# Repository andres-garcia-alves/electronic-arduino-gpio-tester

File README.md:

# Arduino GPIO Tester

Electronic proyect for easy test of Arduino Nano/UNO analog and digital (GPIO) pins.  

&nbsp;

This project use the following electronic components:
- 1 x Arduino Nano v3.0
- 2 x Connector pins
- 22 x LED 3mm
- 22 x 1k ohm resistors

&nbsp;

### Screenshots

| Diagram - Schematics                            | Diagram - PCB                                   |
|-------------------------------------------------|-------------------------------------------------|
|          |                |

| Diagram - PCB Render                            | Diagram - PCB Render                            |
|-------------------------------------------------|-------------------------------------------------|
|      |       |

| Prototype                                       | PCB Manufacturing                               |
|-------------------------------------------------|-------------------------------------------------|
|          |          |

| PCB Assembly                                    | Project Assembly                                |
|-------------------------------------------------|-------------------------------------------------|
|          |          |

| Project Final                                   | Project Final (YouTube video)                   |
|-------------------------------------------------|-------------------------------------------------|
|          |          |

See 'Rescources' sub-folder for more pictures & videos of the project.

&nbsp;

### Version History

v1.0 (2023.05.13) - Initial release.  
v1.1 (2023.05.16) - Bug fixes.  

&nbsp;

This source code is licensed under GPL v3.0  
Please send me your feedback about this project: andres.garcia.alves@gmail.com

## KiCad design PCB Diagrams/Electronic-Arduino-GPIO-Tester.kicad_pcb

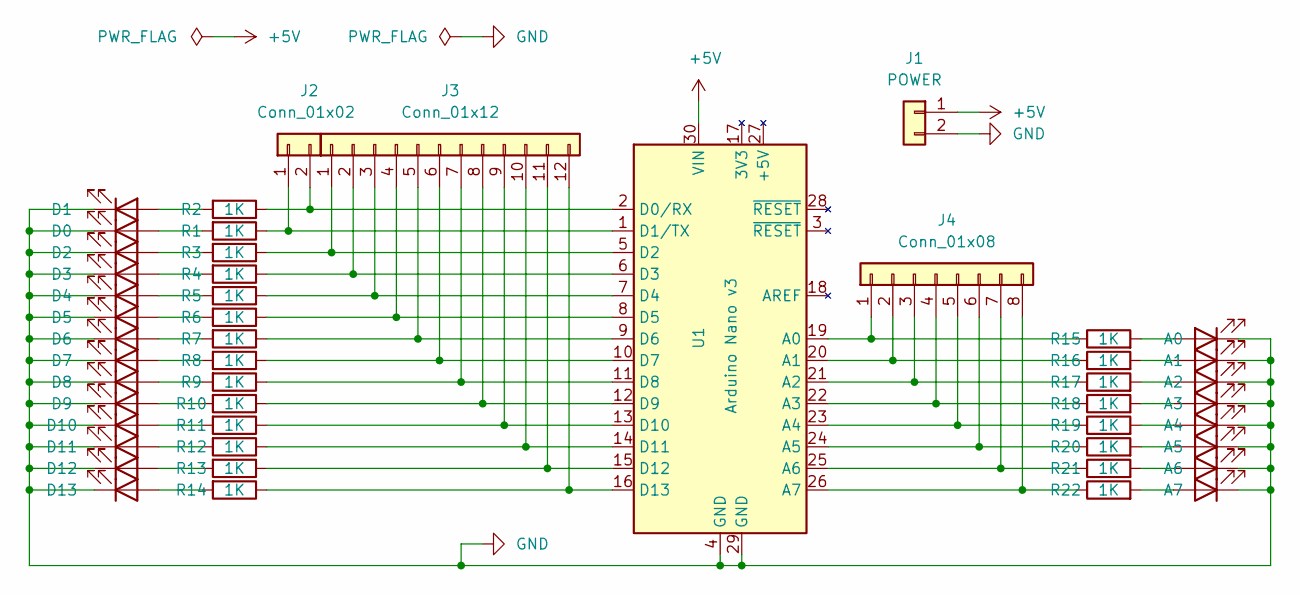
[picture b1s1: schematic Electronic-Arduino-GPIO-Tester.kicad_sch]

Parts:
A0, A1, A2, A3, A4, A5, A6, A7: LED; LED_D3.0mm
D0, D1, D2, D3, D4, D5, D6, D7, D8, D9, D10, D11, D12, D13: LED; LED_D3.0mm
J1: POWER; PinHeader_1x02_P2.54mm_Horizontal
J2: Conn_01x02; PinSocket_1x02_P2.54mm_Vertical
J3: Conn_01x12; PinSocket_1x12_P2.54mm_Vertical
J4: Conn_01x08; PinSocket_1x08_P2.54mm_Vertical
R1, R2, R3, R4, R5, R6, R7, R8, R9, R10, R11, R12, R13, R14, R15, R16, R17, R18, R19, R20, R21, R22: 1K; R_Axial_DIN0207_L6.3mm_D2.5mm_P7.62mm_Horizontal
U1: Arduino Nano v3; Arduino_Nano

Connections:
+5V: J1.1, U1.30 (VIN)
GND: A0.1 (K), A1.1 (K), A2.1 (K), A3.1 (K), A4.1 (K), A5.1 (K), A6.1 (K), A7.1 (K), D0.1 (K), D1.1 (K), D2.1 (K), D3.1 (K), D4.1 (K), D5.1 (K), D6.1 (K), D7.1 (K), D8.1 (K), D9.1 (K), D10.1 (K), D11.1 (K), D12.1 (K), D13.1 (K), J1.2, U1.4 (GND), U1.29 (GND)
unnamed: A0.2 (A), R15.2
unnamed: A1.2 (A), R16.2
unnamed: A2.2 (A), R17.2
unnamed: A3.2 (A), R18.2
unnamed: A4.2 (A), R19.2
unnamed: A5.2 (A), R20.2
unnamed: A6.2 (A), R21.2
unnamed: A7.2 (A), R22.2
unnamed: D0.2 (A), R1.2
unnamed: D1.2 (A), R2.2
unnamed: D2.2 (A), R3.2
unnamed: D3.2 (A), R4.2
unnamed: D4.2 (A), R5.2
unnamed: D5.2 (A), R6.2
unnamed: D6.2 (A), R7.2
unnamed: D7.2 (A), R8.2
unnamed: D8.2 (A), R9.2
unnamed: D9.2 (A), R10.2
unnamed: D10.2 (A), R11.2
unnamed: D11.2 (A), R12.2
unnamed: D12.2 (A), R13.2
unnamed: D13.2 (A), R14.2
unnamed: J2.1, R1.1, U1.1 (D1/TX)
unnamed: J2.2, R2.1, U1.2 (D0/RX)
unnamed: J3.1, R3.1, U1.5 (D2)
unnamed: J3.2, R4.1, U1.6 (D3)
unnamed: J3.3, R5.1, U1.7 (D4)
unnamed: J3.4, R6.1, U1.8 (D5)
unnamed: J3.5, R7.1, U1.9 (D6)
unnamed: J3.6, R8.1, U1.10 (D7)
unnamed: J3.7, R9.1, U1.11 (D8)
unnamed: J3.8, R10.1, U1.12 (D9)
unnamed: J3.9, R11.1, U1.13 (D10)
unnamed: J3.10, R12.1, U1.14 (D11)
unnamed: J3.11, R13.1, U1.15 (D12)
unnamed: J3.12, R14.1, U1.16 (D13)
unnamed: J4.1, R15.1, U1.19 (A0)
unnamed: J4.2, R16.1, U1.20 (A1)
unnamed: J4.3, R17.1, U1.21 (A2)
unnamed: J4.4, R18.1, U1.22 (A3)
unnamed: J4.5, R19.1, U1.23 (A4)
unnamed: J4.6, R20.1, U1.24 (A5)
unnamed: J4.7, R21.1, U1.25 (A6)
unnamed: J4.8, R22.1, U1.26 (A7)

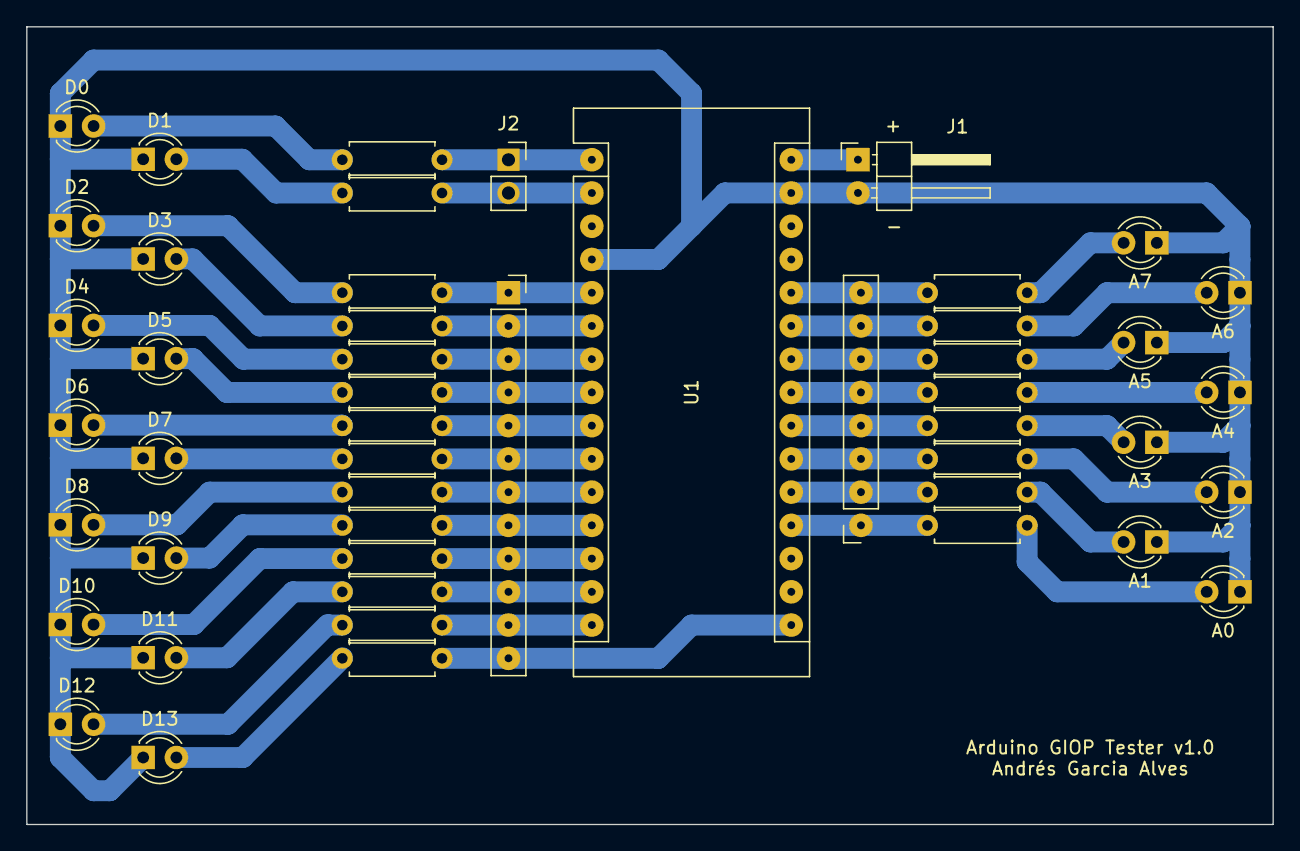
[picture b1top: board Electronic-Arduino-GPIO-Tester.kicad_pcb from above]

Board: 2 copper layers, 95.2 x 61.0 mm, 49 parts (0 on the bottom side), 46 nets.

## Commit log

2023-05-13 Create LICENSE
2023-05-14 adding electronic diagrams
2023-05-14 pcb size optimization
2023-05-16 bug fixes
2023-05-16 update Resources directory
